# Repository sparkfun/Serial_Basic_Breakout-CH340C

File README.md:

SparkFun Serial Basic Breakout - CH340C
========================================

[*SparkFun Serial Basic Breakout - CH340C (DEV-15096)*](https://www.sparkfun.com/products/15096)

This is a CH340C based board that converts USB to Serial. We've added USB-C to
the Serial Basic line which can provide up to 1.5 Amps of power to your next
project. USB-C is also _reversable_, which means you'll never plug in a cable
wrong again. It follows the standard Arduino pin out so this can be used to program the Pro 
and Pro Mini line of Arduinos.  It can also be used as a general serial device for debugging 
(such as with a GPS module).

Board defaults to 3.3V output and 3.3V serial signals, but cutting the trace on the underside of the board and 
soldering a jumper to 5V changes the VCC pin to output 5V and changes serial comm signals to 5V.

Repository Contents
-------------------

* **/Hardware** - Eagle design files (.brd, .sch)
* **/Production** - Production panel files (.brd)

Documentation
--------------

* **[SparkFun Fritzing repo](https://github.com/sparkfun/Fritzing_Parts/blob/main/products/15096_sparkfun_serial_basic_breakout_ch340c_usb_c.fzpz)** - Fritzing diagrams for SparkFun products.
* **[How to Install CH340 Drivers](https://www.sparkfun.com/ch340)** - Drivers if you need
* **[Hookup Guide](https://learn.sparkfun.com/tutorials/serial-basic-hookup-guide)** - Basic hookup guide

License Information
-------------------

This product is _**open source**_! 

Please review the LICENSE.md file for license information. 

If you have any questions or concerns on licensing, please contact techsupport@sparkfun.com.

Distributed as-is; no warranty is given.

- Your friends at SparkFun.

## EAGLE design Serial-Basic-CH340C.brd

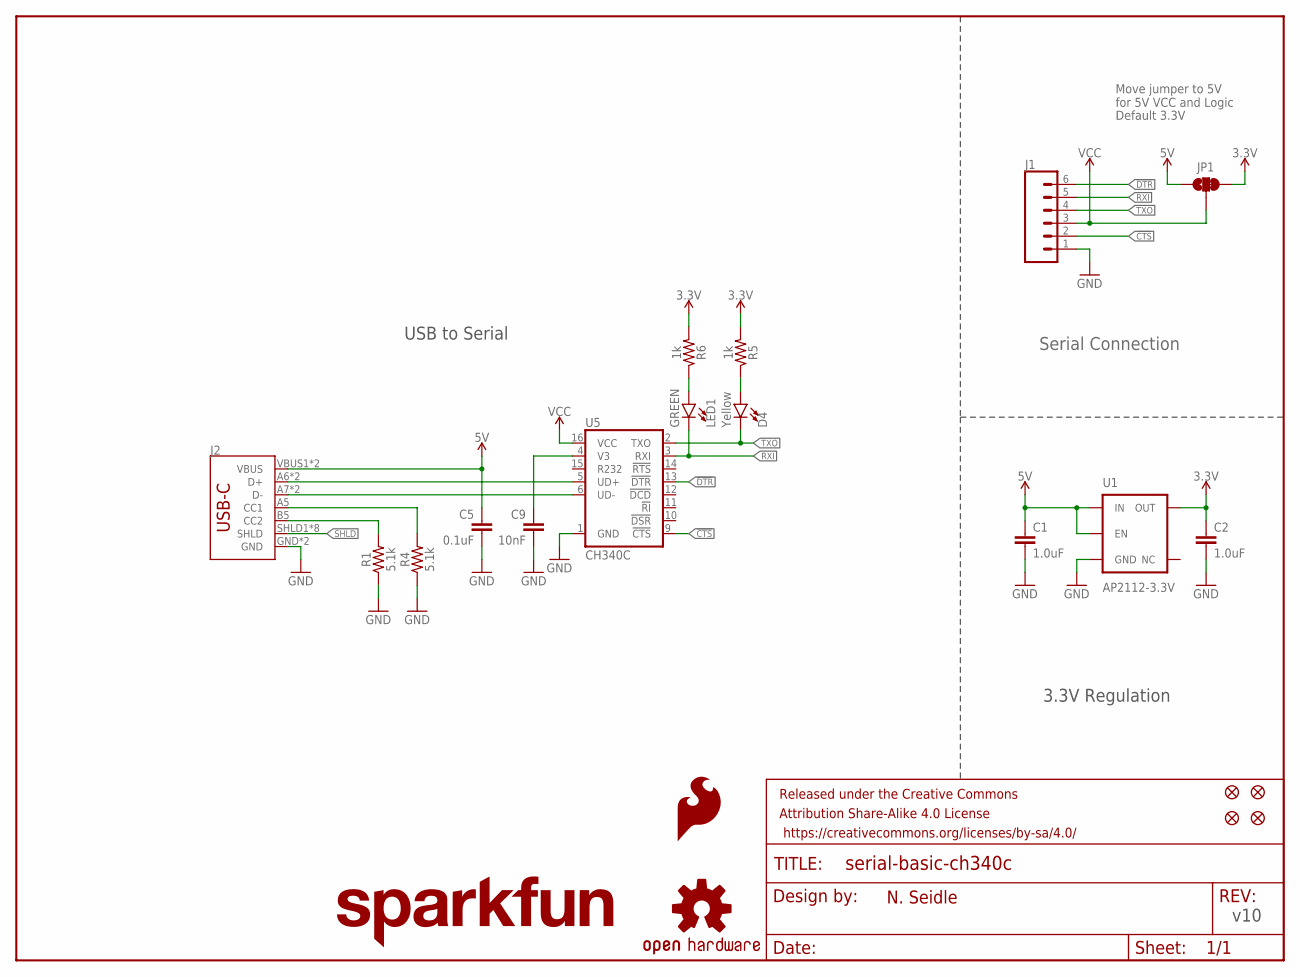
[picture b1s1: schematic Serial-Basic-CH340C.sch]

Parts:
C1, C2: 1.0uF; 0603
C5: 0.1uF; 0603
C9: 10nF; 0603
D4: Yellow; LED-0603
FRAME1: FRAME-LETTER; CREATIVE_COMMONS
J1: CONN_06SMD-FEMALE-V2; 1X06-SMD-FEMALE
J2: USB_C16PIN; USB-C-16P
JP1: JUMPER-SMT_3_1-NC_TRACE_SILK; SMT-JUMPER_3_1-NC_TRACE_SILK
JP3, JP4, JP5, JP6: FIDUCIAL1X2; FIDUCIAL-1X2
LED1: GREEN; LED-0603
LOGO1: OSHW-LOGOS; OSHW-LOGO-S
LOGO2: SFE_LOGO_FLAME.1_INCH; SFE_LOGO_FLAME_.1
LOGO3: SFE_LOGO_NAME.1_INCH; SFE_LOGO_NAME_.1
R1, R4: 5.1k; 0603
R5, R6: 1k; 0603
U1: AP2112-3.3V; SOT23-5
U5: CH340C; SO016

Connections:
3.3V: C2.1, JP1.3, R5.2, R6.2, U1.5 (OUT)
5V: C1.1, C5.1, J2.VBUS1 (VBUS), J2.VBUS2 (VBUS), JP1.1, U1.1 (IN), U1.3 (EN)
!CTS: J1.2, U5.9 (!CTS)
!DTR: J1.6, U5.13 (!DTR)
CC1: J2.A5 (CC1), R4.2
CC2: J2.B5 (CC2), R1.2
D+: J2.A6 (D+), J2.B6 (D+), U5.5 (UD+)
D-: J2.A7 (D-), J2.B7 (D-), U5.6 (UD-)
GND: C1.2, C2.2, C5.2, C9.2, J1.1, J2.GND, J2.GND2 (GND), R1.1, R4.1, U1.2 (GND), U5.1 (GND)
unnamed: C9.1, U5.4 (V3)
unnamed: LED1.A, R6.1
unnamed: D4.A, R5.1
RXI: J1.5, LED1.C, U5.3 (RXI)
SHLD: J2.SHLD1 (SHLD), J2.SHLD2 (SHLD), J2.SHLD3 (SHLD), J2.SHLD4 (SHLD), J2.SHLD5 (SHLD), J2.SHLD6 (SHLD), J2.SHLD7 (SHLD), J2.SHLD8 (SHLD)
TXO: D4.C, J1.4, U5.2 (TXO)
VCC: J1.3, JP1.2, U5.16 (VCC)

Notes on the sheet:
Default 3.3V
v10
USB to Serial
3.3V Regulation
N. Seidle
Move jumper to 5V for 5V VCC and Logic
Serial Connection

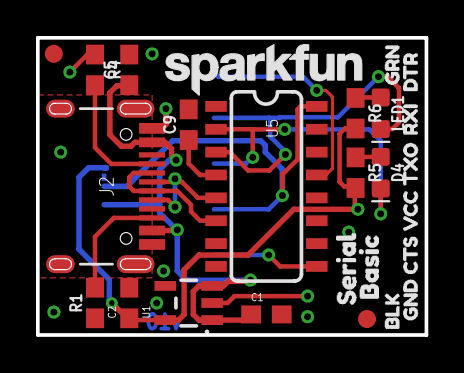
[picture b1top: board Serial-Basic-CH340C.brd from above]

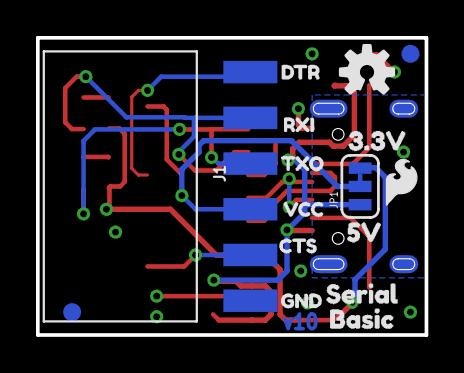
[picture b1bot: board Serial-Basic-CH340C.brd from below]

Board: 2 copper layers, 21.6 x 16.5 mm, 43 parts (16 on the bottom side), 16 nets.

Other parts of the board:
U$1, U$14: CTS1
U$2: 3#3V8
U$3: 5V9
U$4, U$9: SERIAL0
U$5, U$12: TXO0
U$6, U$13: VCC2
U$7, U$11: BASIC1
U$8, U$18: DTR0
U$10, U$21: RXI1
U$15, U$19: GND5
U$17: BLK6
U$20: GRN7

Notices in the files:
parts and their libraries:
SparkFun-Aesthetics: Licensing: CC v3.0 Share-Alike You are welcome to use this library for commercial purposes.
SparkFun-Capacitors: Licensing: Creative Commons ShareAlike 4.0 International - https://creativecommons.org/licenses/by-sa/4.0
SparkFun-Aesthetics: Released under the Creative Commons
